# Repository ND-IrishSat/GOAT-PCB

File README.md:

# GoatLab 
## Arduino Hat PCB
---
This is the PCB hat for the GoatLab Helmholtz Cage main circuit intended to compact the circuit, connecting the power supply, Arduino, and H-Bridges connecting to the cage. 

### PCB Schematic:

### PCB Design: 

### Orthographic View:

## Magnetometer PCB
---
This PCB is intended to compact the magnetometer with the Arduino with an LED to indicate power is reaching the sensor.

### PCB Schematic (by Tyler Hanson):

### PCB Design: 

### Orthographic View:

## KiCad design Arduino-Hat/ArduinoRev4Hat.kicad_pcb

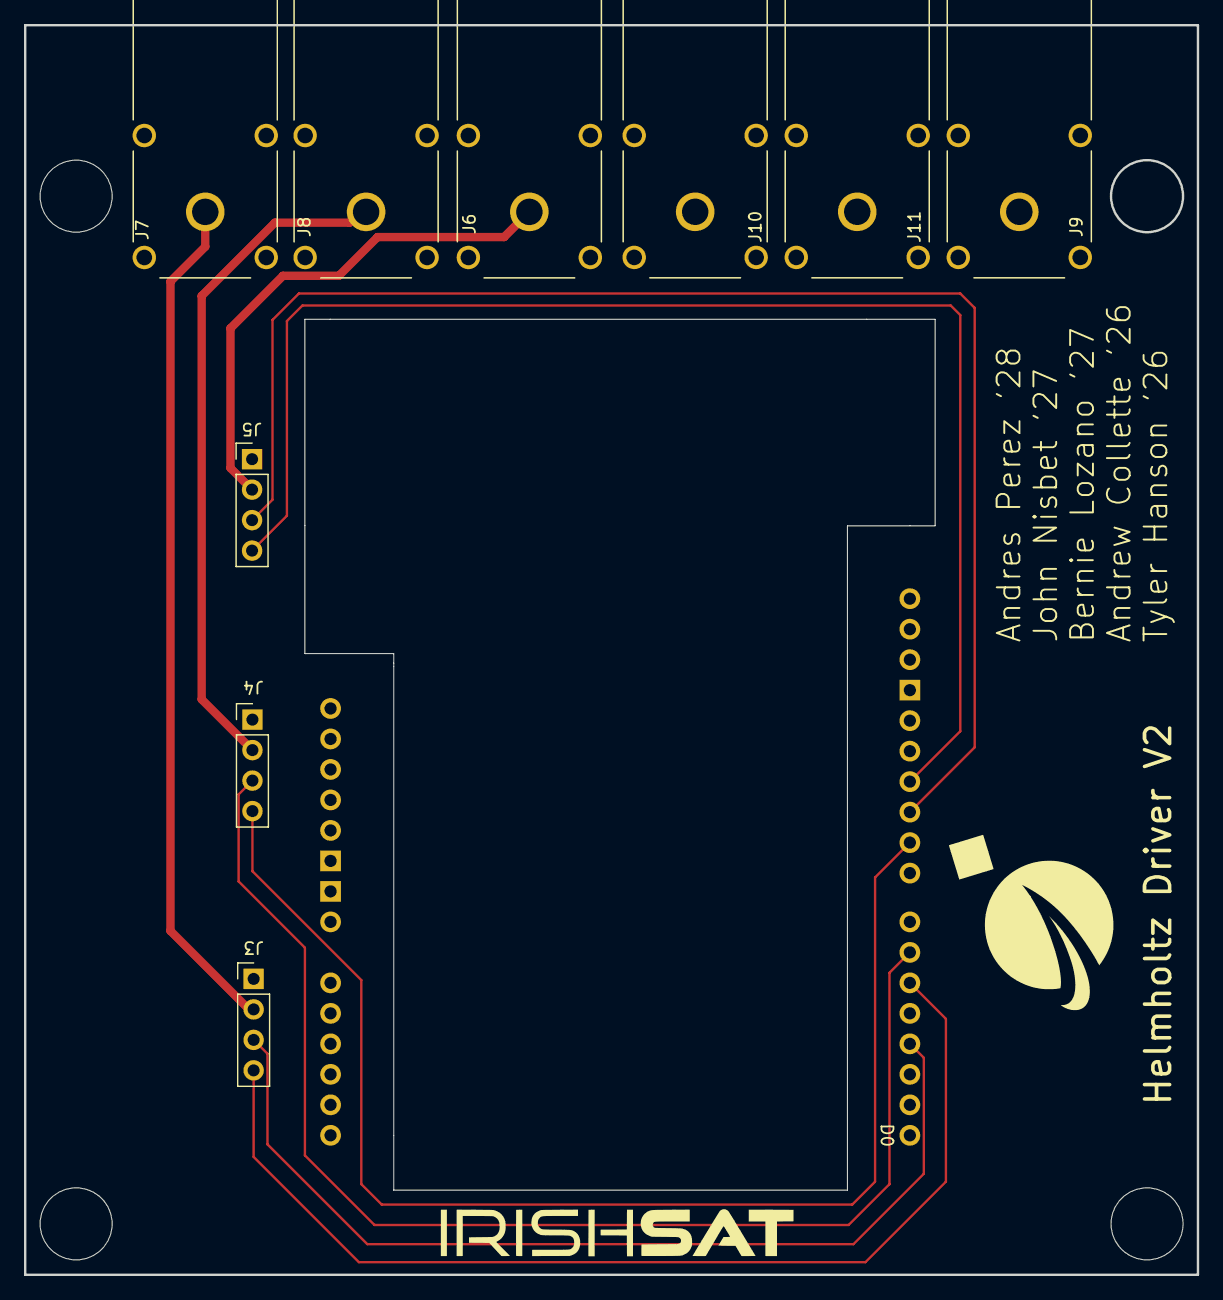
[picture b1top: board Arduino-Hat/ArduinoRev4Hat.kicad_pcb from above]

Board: 2 copper layers, 97.7 x 104.1 mm, 10 parts (0 on the bottom side), 10 nets.

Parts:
A1: Arduino_Uno_R4_WiFi_Shield
J3, J4, J5: Conn_01x04_Pin; PinHeader_1x04_P2.54mm_Vertical
J6, J7, J8, J9, J10, J11: 73099-0; POMONA_73099-0

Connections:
/IN1_X: A1.D10, J5.3
/IN1_Y: A1.D6, J4.3
/IN1_Z: A1.D3, J3.3
/IN2_X: A1.D11, J5.4
/IN2_Y: A1.D9, J4.4
/IN2_Z: A1.D5, J3.4
/VM_X: J5.2, J6.1
/VM_Y: J4.2, J8.1
/VM_Z: J3.2, J7.1
GND: A1.GND1 (GND), A1.GND2 (GND), J3.1, J4.1, J5.1, J9.1, J10.1, J11.1

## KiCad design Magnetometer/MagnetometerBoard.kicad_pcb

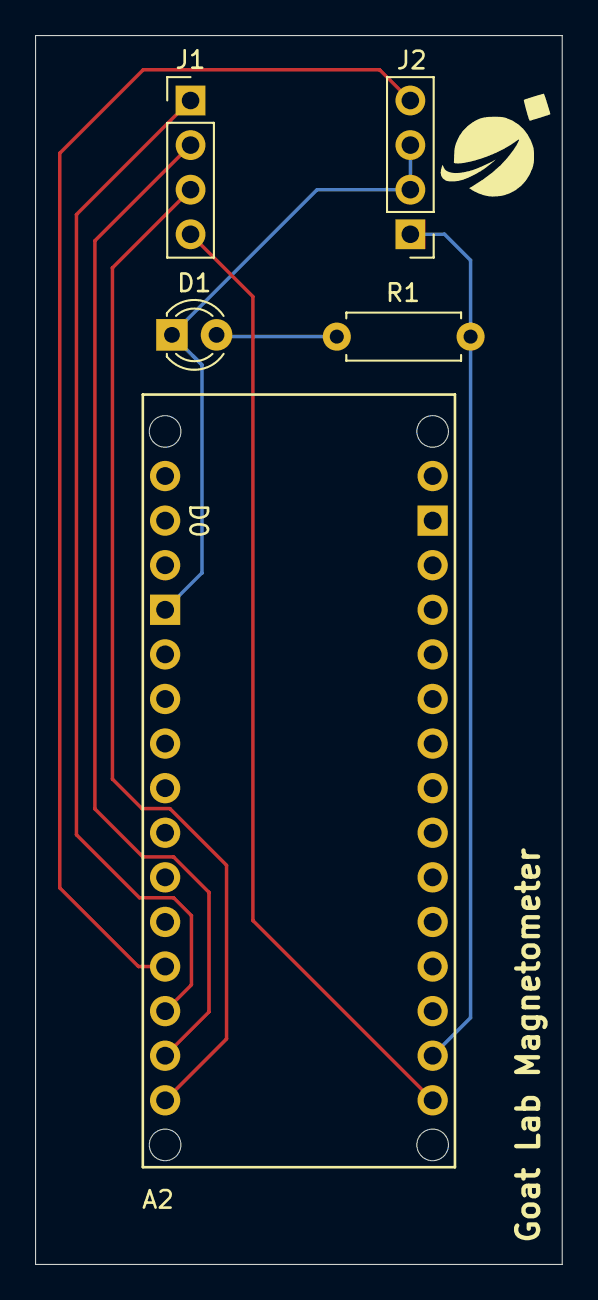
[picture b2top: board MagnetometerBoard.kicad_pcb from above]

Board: 2 copper layers, 30.0 x 70.0 mm, 5 parts (0 on the bottom side), 7 nets.

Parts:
A2: Arduino_Nano_33_IoT_Socket
D1: GREEN LED; LED_D3.0mm
J1, J2: Conn_01x04_Socket; PinHeader_1x04_P2.54mm_Vertical
R1: R; R_Axial_DIN0207_L6.3mm_D2.5mm_P7.62mm_Horizontal

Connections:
+3.3V: A2.3V3 (3.3V), D1.2 (A), J2.1, R1.1, R1.2
/CLK: A2.D13 (D13_SCK), J1.4
/DRDY: A2.D9, J2.4
/MISO: A2.D12 (D12_MISO), J1.3
/MOSI: A2.D11 (D11_MOSI), J1.2
/SSN: A2.D10, J1.1
GND: J2.2, J2.3

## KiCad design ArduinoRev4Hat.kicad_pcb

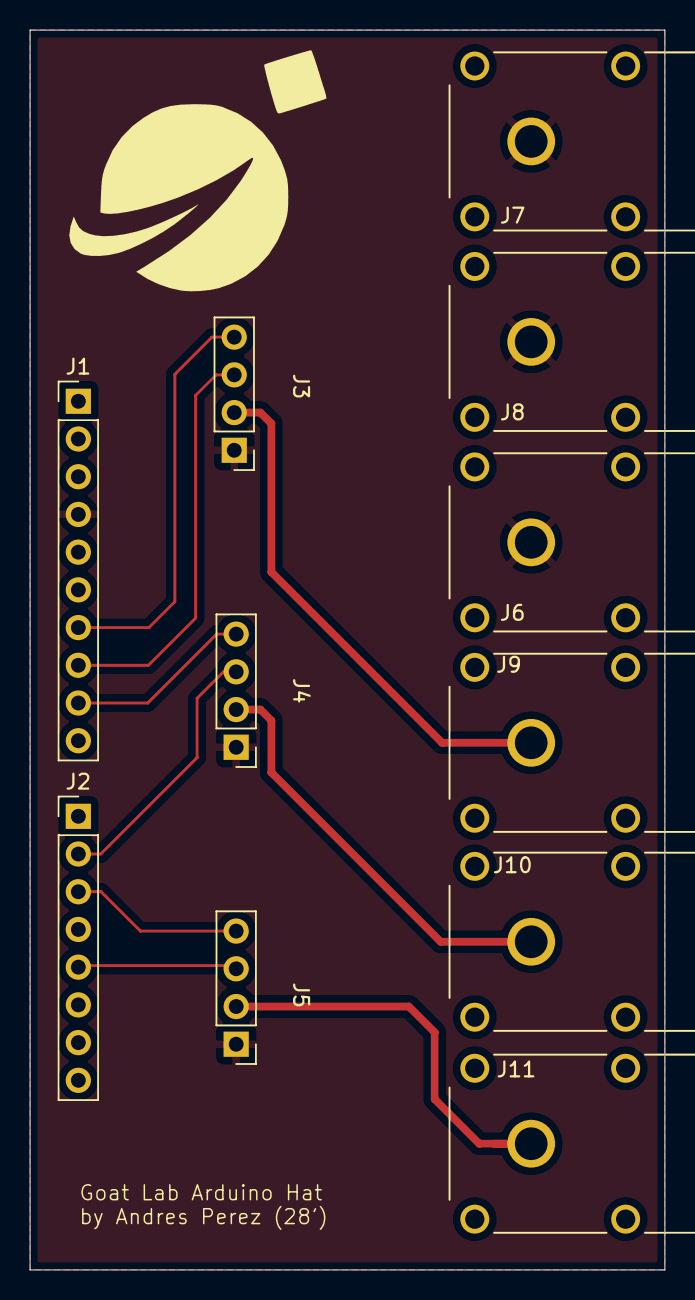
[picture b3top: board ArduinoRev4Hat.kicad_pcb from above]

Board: 2 copper layers, 42.8 x 83.5 mm, 11 parts (0 on the bottom side), 10 nets.

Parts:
J1: Conn_01x10_Pin; PinHeader_1x10_P2.54mm_Vertical
J2: Conn_01x08_Pin; PinHeader_1x08_P2.54mm_Vertical
J3, J4, J5: Conn_01x04_Pin; PinHeader_1x04_P2.54mm_Vertical
J6, J7, J8, J9, J10, J11: 73099-0; POMONA_73099-0

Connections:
/IN1_X: J1.8, J3.3
/IN1_Y: J2.2, J4.3
/IN1_Z: J2.5, J5.3
/IN2_X: J1.7, J3.4
/IN2_Y: J1.9, J4.4
/IN2_Z: J2.3, J5.4
/VM_X: J3.2, J9.1
/VM_Y: J4.2, J10.1
/VM_Z: J5.2, J11.1
GND: J1.4, J3.1, J4.1, J5.1, J6.1, J7.1, J8.1

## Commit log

2024-12-03 testing repo
2024-12-03 testing uploading KiCAD files
2024-12-04 12/3/2024 meeting start of KiCAD file; will implement later tonight
2024-12-04 First attempted at wiring; waiting for Tyler's Review
2024-12-05 Layed out the board. Still awaiting review
2024-12-05 uploading diagram
2025-01-07 Added a ground plane to the PCB plus added .gitignore
2025-01-07 Stopped tracking cache file
2025-01-07 Testing git ignore
2025-01-18 updated the layout of the pcb; added logo and credits; investaged potential components for the print
2025-01-19 changed logo; moved banana plugs location; swaped in1_x and in2_x pin for a better layout;
2025-01-20 change track distance so that high frequencies they could cause some interference with each other
2025-01-21 new ground plane
2025-01-22 basic layout started; need to optimize traces and quality of life addition
2025-01-25 finailzied prototype for the magnetometer pcb
2025-01-26 added logo + title
2025-02-02 no trap
2025-03-10 updates pcb for arduino
2025-04-02 newest version
2025-06-13 updated arduino hat images
